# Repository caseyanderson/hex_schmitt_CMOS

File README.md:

# hex_schmitt_CMOS
PCB files for Hex Schmitt Trigger Synth

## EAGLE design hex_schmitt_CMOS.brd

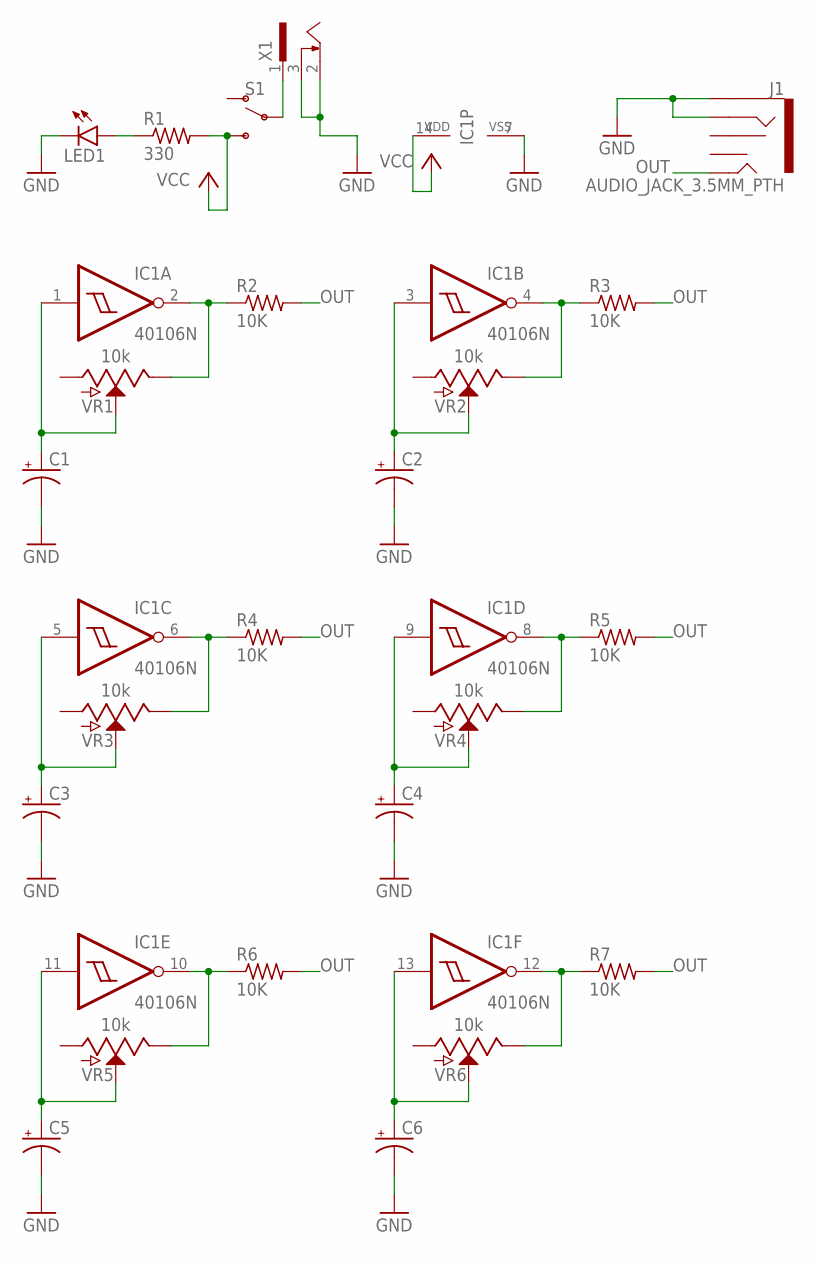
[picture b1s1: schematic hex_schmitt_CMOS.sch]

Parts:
C1, C2, C3, C4, C5, C6: CPOL-USE1.8-4; E1,8-4
IC1: 40106N; DIL14
J1: AUDIO_JACK_3.5MM_PTH; AUDIO-JACK
LED1: LED5MM
R1: 330; 0204/5
R2, R3, R4, R5, R6, R7: 10K; 0204/5
S1: SWITCH-SPDT-PTH-11.6X4.0MM-LOCK; SWITCH_SPDT_PTH_11.6X4.0MM_LOCK
VR1, VR2, VR3, VR4, VR5, VR6: 10k; POT-PTH-ALPS
X1: SCD-014A; SCD-014-A

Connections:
GND: C1.-, C2.-, C3.-, C4.-, C5.-, C6.-, IC1.7 (VSS), J1.RING, J1.SLEEVE, LED1.K (C), X1.2, X1.3
unnamed: S1.2, X1.1
unnamed: C1.+, IC1.1 (I), VR1.P$2 (S)
unnamed: LED1.A, R1.1
unnamed: IC1.2 (O), R2.1, VR1.P$1 (E)
unnamed: C2.+, IC1.3 (I), VR2.P$2 (S)
unnamed: IC1.4 (O), R3.1, VR2.P$1 (E)
unnamed: C3.+, IC1.5 (I), VR3.P$2 (S)
unnamed: IC1.6 (O), R4.1, VR3.P$1 (E)
unnamed: C4.+, IC1.9 (I), VR4.P$2 (S)
unnamed: IC1.8 (O), R5.1, VR4.P$1 (E)
unnamed: C5.+, IC1.11 (I), VR5.P$2 (S)
unnamed: IC1.10 (O), R6.1, VR5.P$1 (E)
unnamed: C6.+, IC1.13 (I), VR6.P$2 (S)
unnamed: IC1.12 (O), R7.1, VR6.P$1 (E)
OUT: J1.TIP, R2.2, R3.2, R4.2, R5.2, R6.2, R7.2
VCC: IC1.14 (VDD), R1.2, S1.3 (S)

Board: 2 copper layers, 24 parts (0 on the bottom side), 17 nets, no tracks yet.

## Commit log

2020-01-10 placeholder README
2020-01-10 adds GNU GENERAL PUBLIC LICENSE to repo
2020-01-10 adds sch file, adds preferred parts to sch file
2020-01-10 adds all 40106 pins to .sch
2020-01-14 adds completed 1st draft of schematic, adds .brd file
2020-02-06 v1, single oscillator pcb works
2020-02-06 screw mounts

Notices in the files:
parts and their libraries:
SparkFun-Connectors: Licensing: Creative Commons ShareAlike 4.0 International - https://creativecommons.org/licenses/by-sa/4.0
